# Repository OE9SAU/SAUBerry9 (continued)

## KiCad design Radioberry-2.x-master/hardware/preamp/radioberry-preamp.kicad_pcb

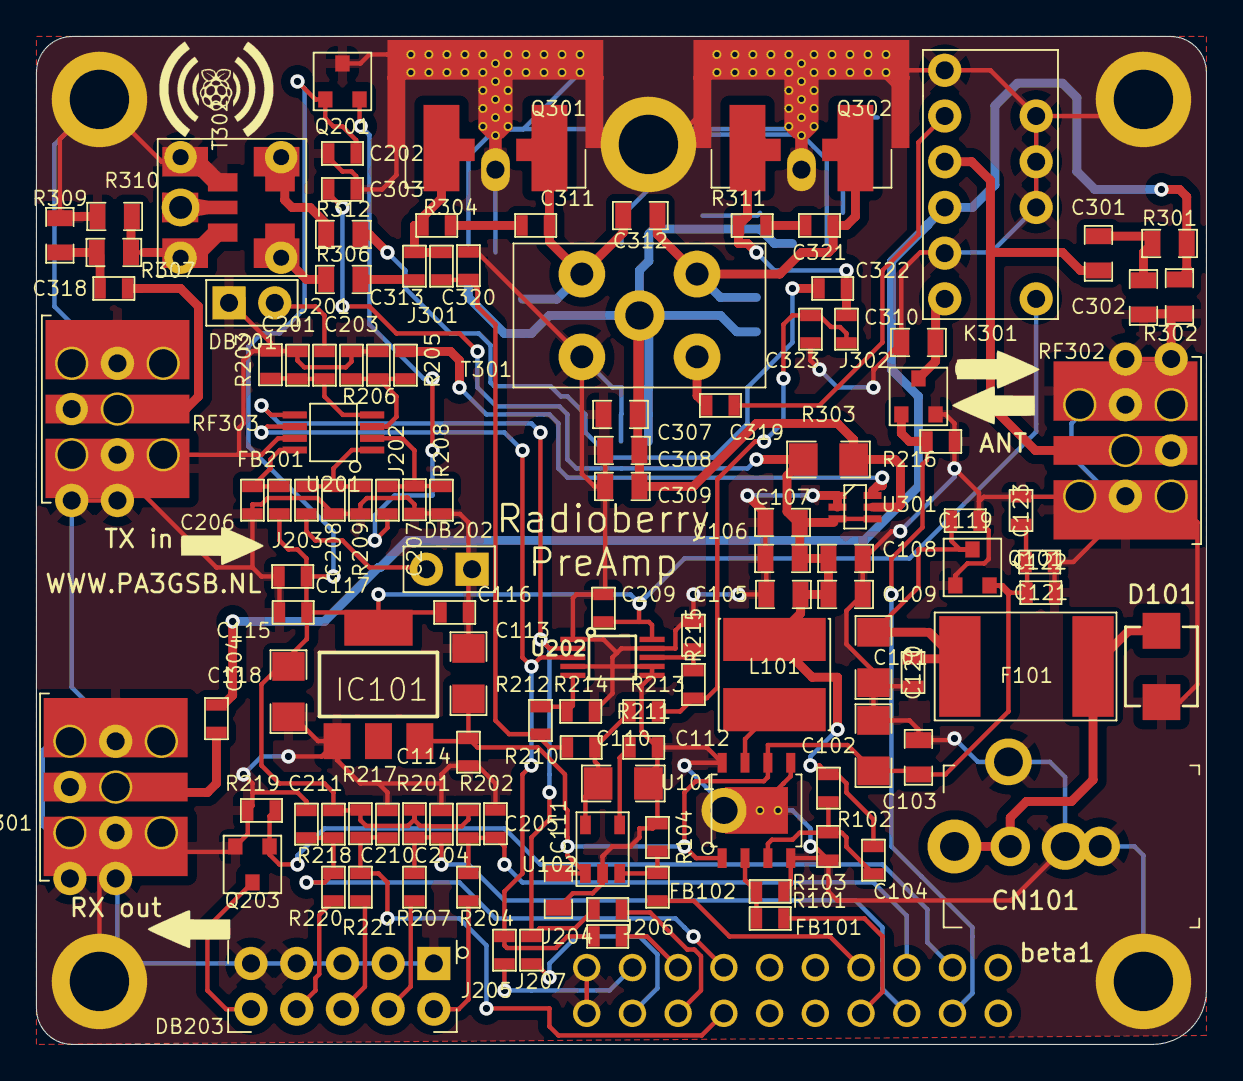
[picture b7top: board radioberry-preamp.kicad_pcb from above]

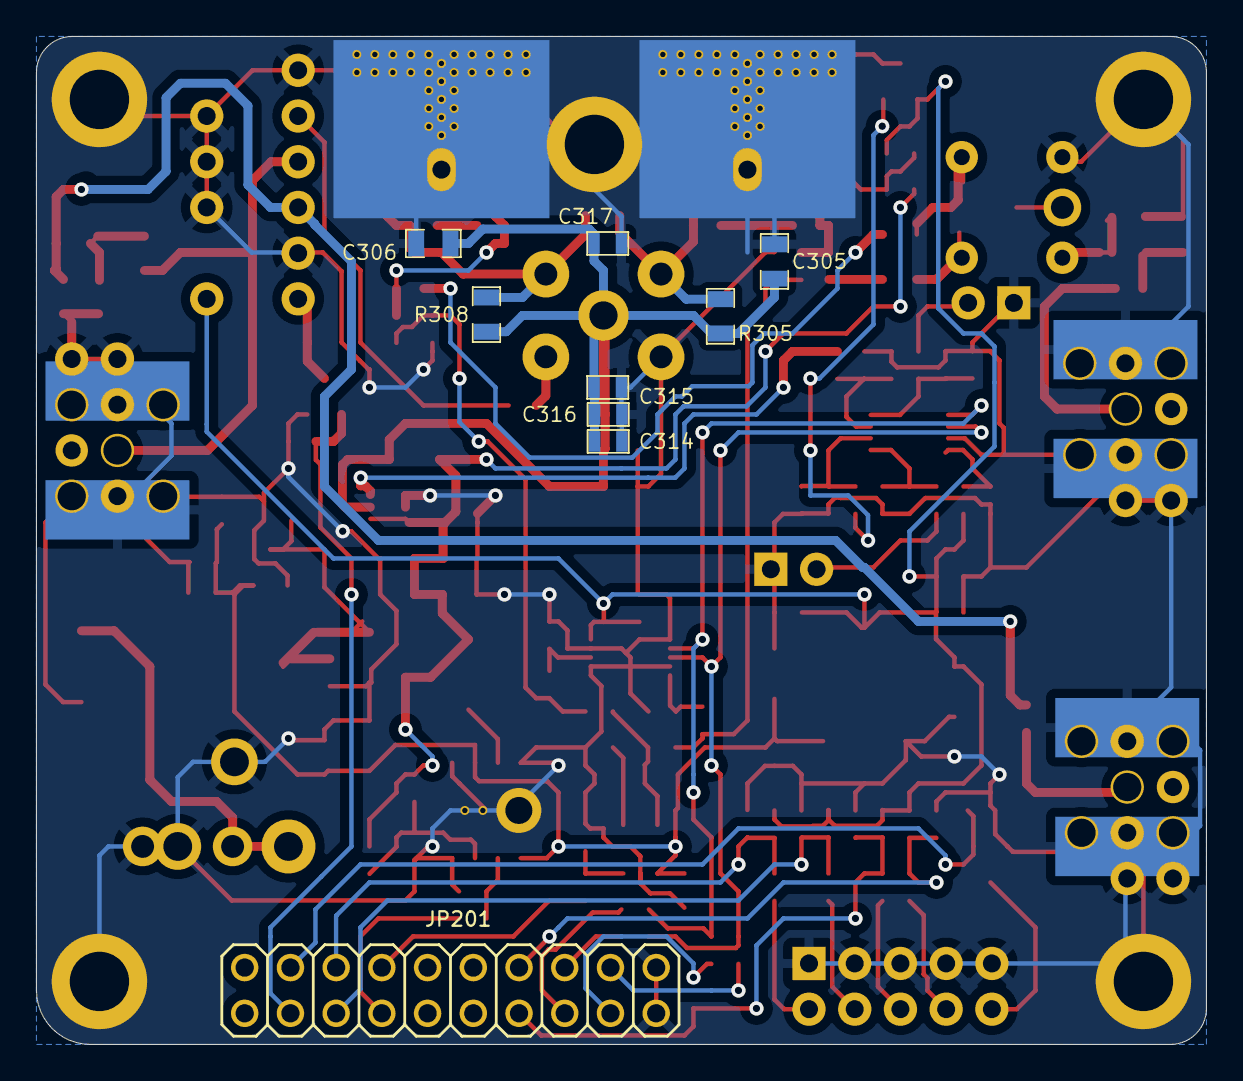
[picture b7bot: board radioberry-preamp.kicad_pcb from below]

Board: 2 copper layers, 65.0 x 56.0 mm, 137 parts (9 on the bottom side), 65 nets.

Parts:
C101, C102, C110, C113: 10uF; SMD-1206
C103: 4.7uF; SMD-0805
C104: 4n7; SMD-0603
C105, C106, C107, C108, C109, C305: 22uF; SMD-0805
C111, C306, C307, C308, C309: 1uF; SMD-0805
C112, C114, C117: 100nF; SMD-0603
C115, C123: 1nF; SMD-0603
C116: 10nF; SMD-0603
C118: 100uF; SMD-1206
C119, C121: 10pF; SMD-0603
C120, C122: 100pF; SMD-0603
C201, C203, C207, C208: 4.7nF; SMD-0603
C202, C206, C209, C303, C304, C311, C313, C314, C315, C316, C317, C318, C319, C320, C321, C322, C323: 0.1uF; SMD-0603
C204, C205, C210, C211: 1uF; SMD-0603
C301, C302: DNI; SMD-0805
C310: 100pF; SMD-0805
C312: 390pF; SMD-0805
CN101: PS; PWRBARREL2
D101: TVSANTI; smbj18ca
DB201, DB202: RFD2b; 2x1
DB203: IO10; 5x2
F101: Polyfuse; FUSE
FB101, FB102, FB201: FB; SMD-0603
IC101: LD1117S33; V-REG_SOT223
J201, J202, J203, J205, J207, J301, J302: JNC; SMD-0603
J204, J206: DNI; SMD-0603
JP201: PINHEAD_PINHD-2X10; PINHEAD_2X10
K301: NA3WK-K; DPDT_GND
L101: 3.3uH; GENERICPSL
MH1, MH2, MH3, MH4, MH5: DNI; m3
Q101: DMP3099L; SOT23_3
Q201: MCP9700; SOT23_3
Q202, Q203: NUD3124; SOT23_3
Q301, Q302: LDMOS; COMBORFGND
R101, R214, R215: 10K; SMD-0603
R102: 16K2; SMD-0603
R103: 1K8; SMD-0603
R104: 4k7; SMD-0603
R201, R202, R217, R218: 2.2K; SMD-0603
R203, R206, R208, R209: 1K; SMD-0603
R204, R207, R220, R221: 100; SMD-0603
R205, R304, R311: 270; SMD-0603
R210, R211: 27K; SMD-0603
R212, R213: 9.1K; SMD-0603
R216, R219: 4.7K; SMD-0603
R301, R302: DNI; SMD-0805
R303: 0.04; SMD-1206
R305, R308: 1K; SMD-0805
R306, R312: 12; SMD-0805
R307: 5.769; SMD-0805
R309, R310: 869.548; SMD-0805
RF301, RF302, RF303: SMA; SMAEDGE_THFULL_L
T301: 4:1 Z; BN202V
T302: 1:1; TRANSFSMT
U101: ST1S10
U102: LP2985; SOT23
U201: MAX11613
U202: MCP4662; SOIC-10
U301: INA199A1DC; PE4259

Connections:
+3V3: C115.1, C116.1, C117.1, C118.1, C202.1, C209.1, FB201.1, IC101.4, K301.1, Q201.1, R201.2, R202.2, R217.2, R218.2, U202.10
+VBIAS: C110.1, R210.2, R211.2, U102.5
+VPA: C104.1, C105.1, C106.1, C107.1, C108.1, C109.1, C303.1, L101.1, R102.1, R303.1, U301.3, U301.4
/Amplifier/ant: C301.1, K301.9, RF302.1
/Control/AIN1: DB202.2, J203.2
/Control/AIN2: DB201.2, J201.2
EXTDASH: DB203.4, R207.2
EXTDOT: DB203.2, R204.2
EXTKEY: DB203.6, R221.2
EXTPTT: DB203.8, R220.2
EXTTR: DB203.10, Q203.3
GND: C101.2, C102.2, C103.2, C105.2, C106.2, C107.2, C108.2, C109.2, C110.2, C111.2, C112.2, C113.2, C114.2, C115.2, C116.2, C117.2, C118.2, C119.2, C120.2, C121.2, C122.2, C123.2, C201.2, C202.2, C203.2, C204.2, C205.2, C206.2, C207.2, C208.2, C209.2, C210.2, C211.2, C302.2, C303.2, C305.2, C306.2, C307.2, C308.2, C309.2, C310.2, C314.1, C315.1, C316.1, C317.1, C320.1, C323.1, CN101.2, D101.2, DB201.1, DB202.1, DB203.1, DB203.3, DB203.5, DB203.7, DB203.9, IC101.1, JP201.19, JP201.20, K301.3, K301.4, K301.5, K301.7, K301.11, MH1.1, MH2.1, MH3.1, MH4.1, MH5.1, Q101.1, Q201.3, Q202.2, Q203.2, Q301.2, Q302.2, R101.1, R103.2, R104.1, R203.1, R206.1, R208.1, R209.1, R214.1, R215.1, R216.1, R219.1, R302.1, R309.1, R310.1, RF301.2, RF302.2, RF303.2, T301.5, T302.1, U101.4, U101.5, U101.8, U101.9, U102.2, U201.7, U202.1, U202.4, U202.6, U202.7, U202.9, U301.1, U301.2
INTTR: C310.1, K301.12, Q202.3
unnamed: C101.1, C119.1, C120.1, F101.1, Q101.3
unnamed: C102.1, C103.1, C111.1, C113.1, C114.1, C121.1, C122.1, C123.1, IC101.3, Q101.2, U101.1, U101.6, U102.1
unnamed: C104.2, R102.2, R103.1, U101.3
unnamed: C112.1, U102.4
unnamed: C201.1, J201.1, R203.2, U201.4
unnamed: C203.1, R205.1, R206.2, U201.3
unnamed: C206.1, FB201.2, U201.8
unnamed: C207.1, J202.1, R208.2, U201.2
unnamed: C208.1, J203.1, R209.2, U201.1
unnamed: C301.2, C302.1, R301.2
unnamed: C304.1, K301.10, R301.1, R302.2
unnamed: C304.2, RF301.1
unnamed: C305.1, C306.1, C307.1, C308.1, C309.1, C314.2, C315.2, C316.2, C317.2, R303.2, R305.1, R308.2, T301.2, U301.5
unnamed: C311.1, C312.1, Q301.3, R305.2, T301.1
unnamed: C311.2, R304.1
unnamed: C312.2, C321.1, Q302.3, R308.1, T301.3
unnamed: C313.1, J301.1, Q301.1, R304.2
unnamed: C313.2, R306.1
unnamed: C318.1, R307.2, R309.2
unnamed: C318.2, RF303.1
unnamed: C319.1, K301.8
unnamed: C319.2, T301.4
unnamed: C321.2, R311.1
unnamed: C322.1, J302.1, Q302.1, R311.2
unnamed: C322.2, R312.1
unnamed: CN101.1, D101.1, F101.2
unnamed: FB101.2, R101.2, U101.2
unnamed: FB102.2, R104.2, U102.3
unnamed: L101.2, U101.7
unnamed: R212.1, R214.2, U202.5
unnamed: R213.1, R215.2, U202.8
unnamed: R306.2, T302.4
unnamed: R307.1, R310.2, T302.3
unnamed: R312.2, T302.5
SCL: J206.1, J207.1, U201.5, U202.2
SDA: J204.1, J205.1, U201.6, U202.3
Vipa: R205.2, U301.6
Vtemp: J202.2, Q201.2
bias: FB102.1, JP201.8
bias0: C323.2, J302.2, R211.1, R213.2
bias1: C320.2, J301.2, R210.1, R212.2
dash: C204.1, JP201.5, R201.1, R207.1
dot: C205.1, JP201.6, R202.1, R204.1
envpa: FB101.1, JP201.7
fpga_scl: J206.2, JP201.15
fpga_sda: J204.2, JP201.16
key: C210.1, JP201.13, R217.1, R221.1
ptt: C211.1, JP201.14, R218.1, R220.1
rb_exttr: JP201.4, Q203.1, R219.2
rb_inttr: JP201.3, Q202.1, R216.2
rpi_scl: J207.2, JP201.17
rpi_sda: J205.2, JP201.18

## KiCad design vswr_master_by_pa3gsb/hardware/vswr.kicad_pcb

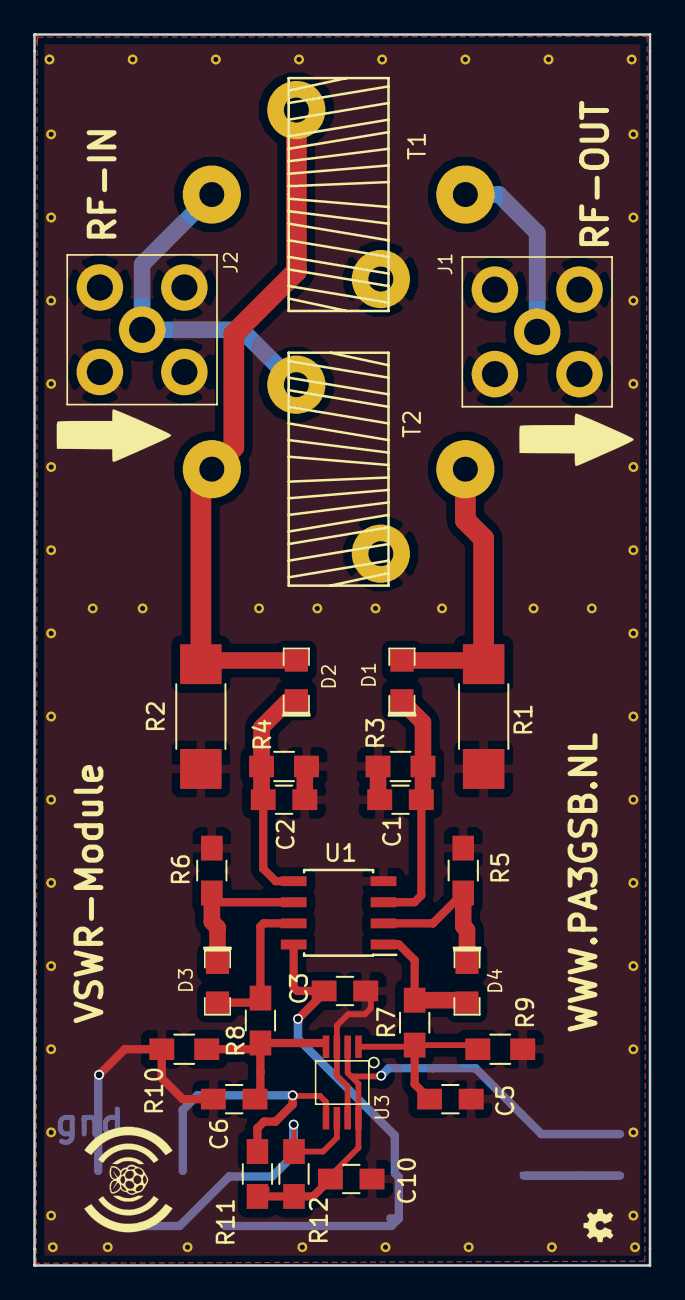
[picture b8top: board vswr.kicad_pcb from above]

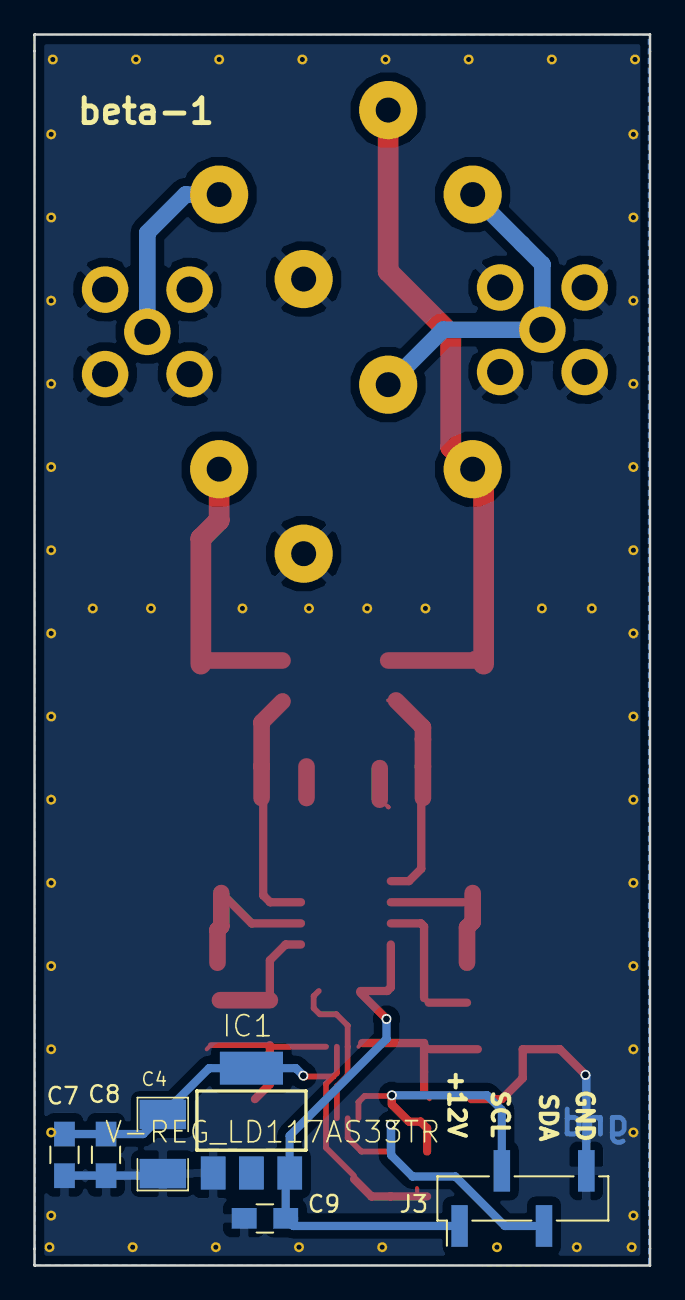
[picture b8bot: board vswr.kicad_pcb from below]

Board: 2 copper layers, 37.0 x 74.0 mm, 34 parts (6 on the bottom side), 17 nets.

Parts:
C1, C2, C3, C10: 100nF; C_0805_HandSoldering
C4: CP; SMD-1210
C5, C6: 10nF; C_0805_HandSoldering
C7, C8, C9: C; C_0805_HandSoldering
D1, D2, D3, D4: 1N5711W-7-F; 1N5711WS
IC1: V-REG_LD117AS33TR; V-REG_SOT223
J1, J2: CONN_COAXIAL; SMAVERT
J3: CONN_01X04; Pin_Header_Straight_1x04_Pitch2.54mm_SMD_Pin1Left
R1, R2: 51.1; R_2010_HandSoldering
R3, R4: 100K; R_0805_HandSoldering
R5, R6: 220K; R_0805_HandSoldering
R7, R8: 1K; R_0805_HandSoldering
R9, R10: 1K8; R_0805_HandSoldering
R11, R12: 4K7; R_0805_HandSoldering
T1, T2: FT50-43; T50-43_V_THT
U1: LMC6482; SOIC-8_3.9x4.9mm_Pitch1.27mm
U3: MAX11613

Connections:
+3V3: C4.1, C7.1, C8.1, C10.2, IC1.4, R11.1, R12.1, U3.2, U3.8
+12V: C3.2, C9.1, IC1.3, J3.1, U1.8
GND: C1.2, C2.1, C3.1, C4.2, C5.2, C6.1, C7.2, C8.2, C9.2, C10.1, IC1.1, J1.2, J2.2, J3.4, R1.1, R2.2, R3.2, R4.1, R5.1, R6.1, R9.2, R10.1, T1.3, T2.4, U1.4, U3.3, U3.7
unnamed: C1.1, D1.2, R3.1, U1.3
unnamed: C2.2, D2.2, R4.2, U1.5
unnamed: C5.1, R7.1, R9.1, U3.1
unnamed: C6.2, R8.1, R10.2, U3.4
unnamed: D1.1, R1.2, T2.1
unnamed: D2.1, R2.1, T1.4, T2.2
unnamed: D3.1, R8.2, U1.7
unnamed: D3.2, R6.2, U1.6
unnamed: D4.1, R7.2, U1.1
unnamed: D4.2, R5.2, U1.2
unnamed: J1.1, T1.2
unnamed: J2.1, T1.1, T2.3
SCL: J3.2, R11.2, U3.5
SDA: J3.3, R12.2, U3.6

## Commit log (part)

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2025-10-25 Repo_Upload
2025-10-26 console_code_update
2025-10-26 some code stuff
2025-10-27 png _upload
2025-10-27 Improve README formatting and emphasis
    Updated formatting for project description in README.
2025-10-27 Fix typo in project name in README.md
2025-10-27 Improve README formatting and project description
    Formatted project description for clarity and readability.
2025-10-27 Revise component statuses in README
    Updated the status of several components to 'in progress'.
2025-10-27 pngs
2025-10-27 Update README to specify touch screen usage
2025-10-27 done some file movement
2025-10-29 Update SDR_PreAmp_Filter entry with GitHub link
    Added link to SDR_PreAmp_Filter GitHub repository.
2025-11-02 some work
2025-11-02 Update version number to v2.1 in README
2025-11-02 Revise README for v2.1 enhancements and bug fixes
    Updated README with changes in v2.1, including encoder direction reversal and gain limits.
2025-11-02 Update README with cloning instructions
    Added instructions for cloning the Radioberry Console repository.
2025-11-02 file update
2025-11-02 upload master
2025-11-02 moved
2025-11-02 front_rework
2025-11-03 back_panel
2025-11-03 some 3d
2025-11-03 some 3d stuff
2025-11-03 back_work
2025-11-04 front_work
2025-11-04 front_pcb
2025-11-04 housing_files
2025-11-05 pwr_board
2025-11-05 pwr_board_work
2025-11-05 pwr_pcb
2025-11-06 files
2025-11-06 latcher_upl
2025-11-06 pwr_latcher
2025-11-06 Update README with Power Latcher details
    Added Power Latcher information to the README.
2025-11-06 file_moving
2025-11-06 letcher_v1
2025-11-06 gerber_latcher_v1
2025-11-07 pcb_layout
2025-11-07 trashing
2025-11-07 extension_pcb
2025-11-07 Revise README for v2 fork and sensor addition
    Updated README to reflect versioning and changes.
2025-11-07 Update README with vswr temp bridge details
    Added a description of the vswr temp bridge project.
2025-11-07 add vswr...
2025-11-07 del repo
2025-11-07 datasheet_upd
2025-11-07 vswr_update
2025-11-14 vswr_pcb
2025-11-20 Commits
2025-11-20 PCB_rework
2025-11-23 Commit_front
2025-11-24 Commit_vswr
2025-11-28 silkscreen_mod
2025-11-28 changings
2025-11-30 PCB changings
2026-01-09 pwr_lachter
2026-01-10 vswr
2026-01-17 PCB_Update
2026-02-28 Messungen
